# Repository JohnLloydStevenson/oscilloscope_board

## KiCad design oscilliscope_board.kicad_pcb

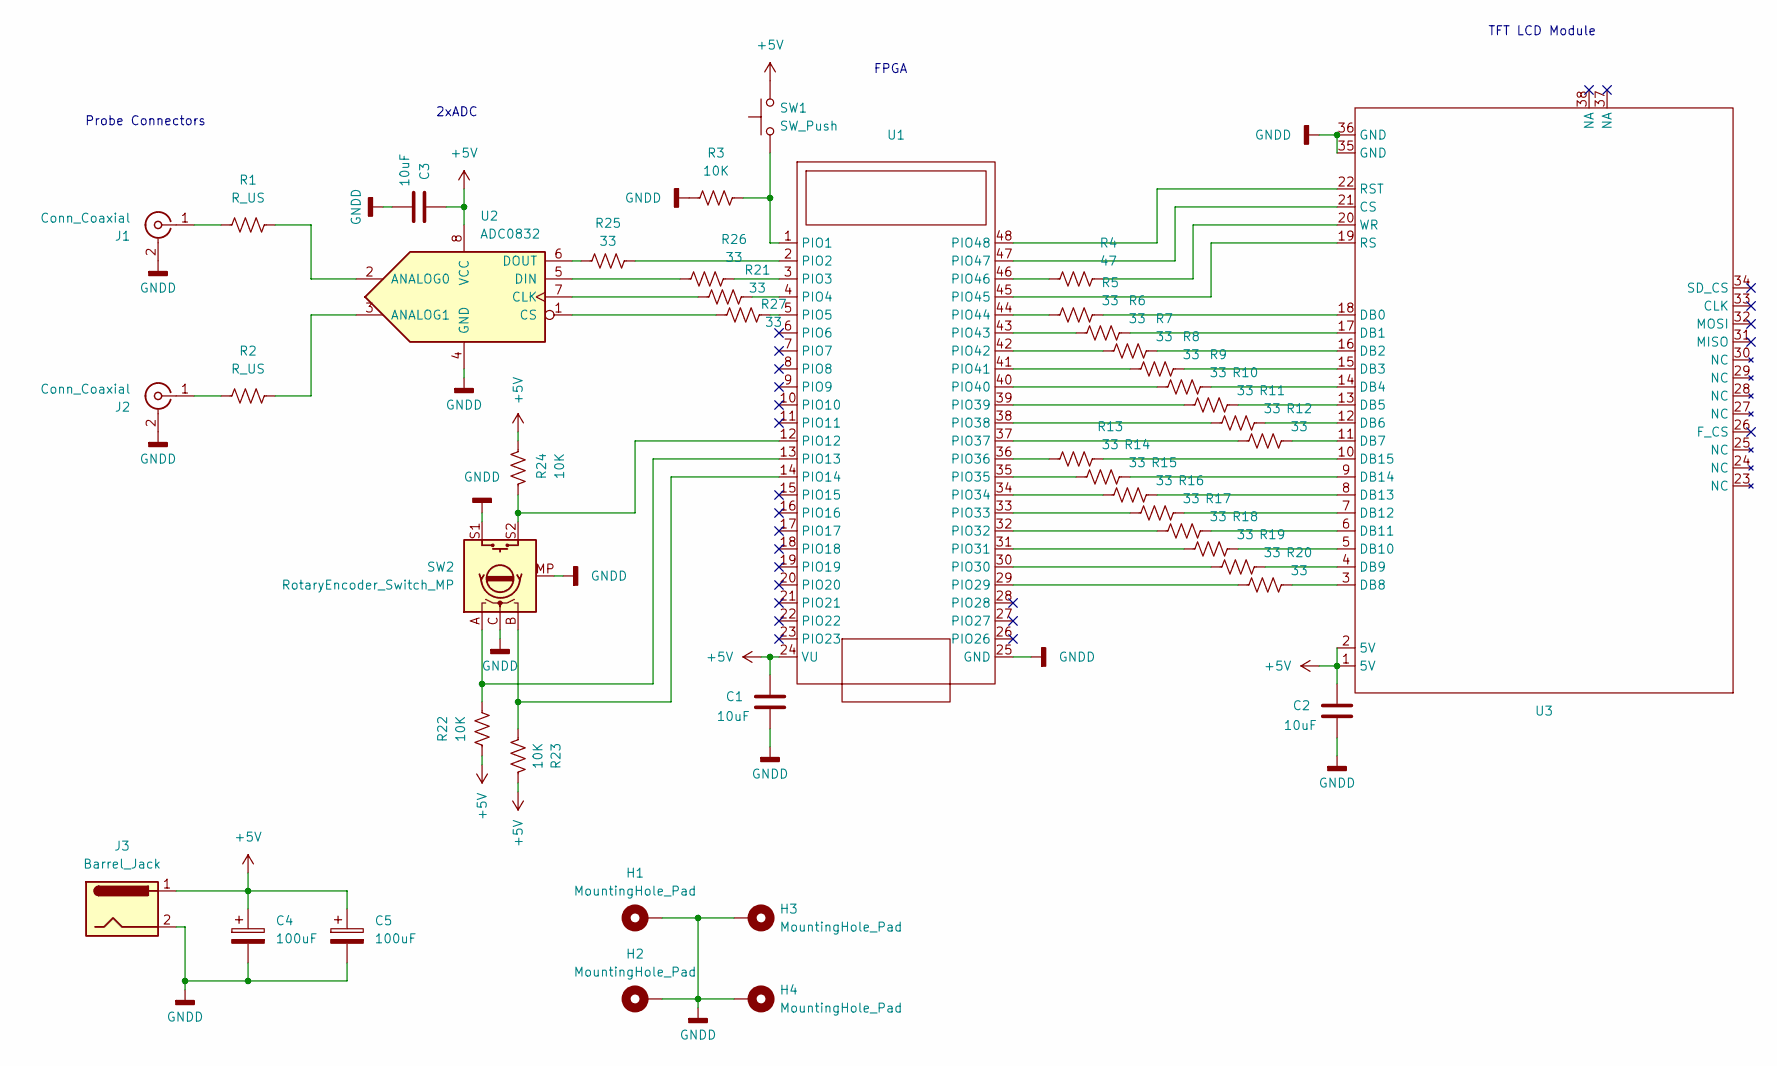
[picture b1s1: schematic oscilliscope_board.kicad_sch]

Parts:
C1, C2, C3: 10uF; C_Disc_D4.7mm_W2.5mm_P5.00mm
C4, C5: 100uF; CP_Radial_D8.0mm_P2.50mm
H1, H2, H3, H4: MountingHole_Pad; MountingHole_3.2mm_M3_DIN965_Pad
J1, J2: Conn_Coaxial; LINX_CONBNC001
J3: Barrel_Jack; BarrelJack_GCT_DCJ200-10-A_Horizontal
R1, R2: R_US; R_0805_2012Metric_Pad1.20x1.40mm_HandSolder
R3: 10K; R_1206_3216Metric_Pad1.30x1.75mm_HandSolder
R4: 47; R_0805_2012Metric_Pad1.20x1.40mm_HandSolder
R5, R6, R7, R8, R9, R10, R11, R12, R13, R14, R15, R16, R17, R18, R19, R20, R21, R25, R26, R27: 33; R_0805_2012Metric_Pad1.20x1.40mm_HandSolder
R22, R23, R24: 10K; R_0805_2012Metric_Pad1.20x1.40mm_HandSolder
SW1: SW_Push; SW_Cherry_MX_1.00u_Plate
SW2: RotaryEncoder_Switch_MP; RotaryEncoder_Bourns_Vertical_PEC12R-3x17F-Sxxxx
U1: Cmod A7 35T CPG236
U2: ADC0832; CERDIP-8_W7.62mm_SideBrazed
U3: TFT LCD 3.5 ArduinoMega Shield

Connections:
+5V: C1.1, C2.1, C3.1, C4.1, C5.1, J3.1, R22.1, R23.1, R24.1, SW1.2, U1.24 (VU), U2.8 (VCC), U3.1 (5V), U3.2 (5V)
GNDD: C1.2, C2.2, C3.2, C4.2, C5.2, H1.1, H2.1, H3.1, H4.1, J1.2 (Ext), J2.2 (Ext), J3.2, R3.1, SW2.C, SW2.MP, SW2.S1, U1.25 (GND), U2.4 (GND), U3.35 (GND), U3.36 (GND)
unnamed: J1.1 (In), R1.1
unnamed: J2.1 (In), R2.1
unnamed: R3.2, SW1.1, U1.1 (PIO1)
unnamed: R25.2, U1.2 (PIO2)
unnamed: R26.2, U1.3 (PIO3)
unnamed: R21.2, U1.4 (PIO4)
unnamed: R27.2, U1.5 (PIO5)
unnamed: R24.2, SW2.S2, U1.12 (PIO12)
unnamed: R22.2, SW2.A, U1.13 (PIO13)
unnamed: R23.2, SW2.B, U1.14 (PIO14)
unnamed: R20.1, U1.29 (PIO29)
unnamed: R19.1, U1.30 (PIO30)
unnamed: R18.1, U1.31 (PIO31)
unnamed: R17.1, U1.32 (PIO32)
unnamed: R16.1, U1.33 (PIO33)
unnamed: R15.1, U1.34 (PIO34)
unnamed: R14.1, U1.35 (PIO35)
unnamed: R13.1, U1.36 (PIO36)
unnamed: R12.1, U1.37 (PIO37)
unnamed: R11.1, U1.38 (PIO38)
unnamed: R10.1, U1.39 (PIO39)
unnamed: R9.1, U1.40 (PIO40)
unnamed: R8.1, U1.41 (PIO41)
unnamed: R7.1, U1.42 (PIO42)
unnamed: R6.1, U1.43 (PIO43)
unnamed: R5.1, U1.44 (PIO44)
unnamed: U1.45 (PIO45), U3.19 (RS)
unnamed: R4.1, U1.46 (PIO46)
unnamed: U1.47 (PIO47), U3.21 (CS)
unnamed: U1.48 (PIO48), U3.22 (RST)
unnamed: R1.2, U2.2 (ANALOG0)
unnamed: R2.2, U2.3 (ANALOG1)
unnamed: R21.1, U2.7 (CLK)
unnamed: R27.1, U2.1 (CS)
unnamed: R26.1, U2.5 (DIN)
unnamed: R25.1, U2.6 (DOUT)
unnamed: R5.2, U3.18 (DB0)
unnamed: R6.2, U3.17 (DB1)
unnamed: R7.2, U3.16 (DB2)
unnamed: R8.2, U3.15 (DB3)
unnamed: R9.2, U3.14 (DB4)
unnamed: R10.2, U3.13 (DB5)
unnamed: R11.2, U3.12 (DB6)
unnamed: R12.2, U3.11 (DB7)
unnamed: R20.2, U3.3 (DB8)
unnamed: R19.2, U3.4 (DB9)
unnamed: R18.2, U3.5 (DB10)
unnamed: R17.2, U3.6 (DB11)
unnamed: R16.2, U3.7 (DB12)
unnamed: R15.2, U3.8 (DB13)
unnamed: R14.2, U3.9 (DB14)
unnamed: R13.2, U3.10 (DB15)
unnamed: R4.2, U3.20 (WR)

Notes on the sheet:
TFT LCD Module
Probe Connectors
FPGA
2xADC

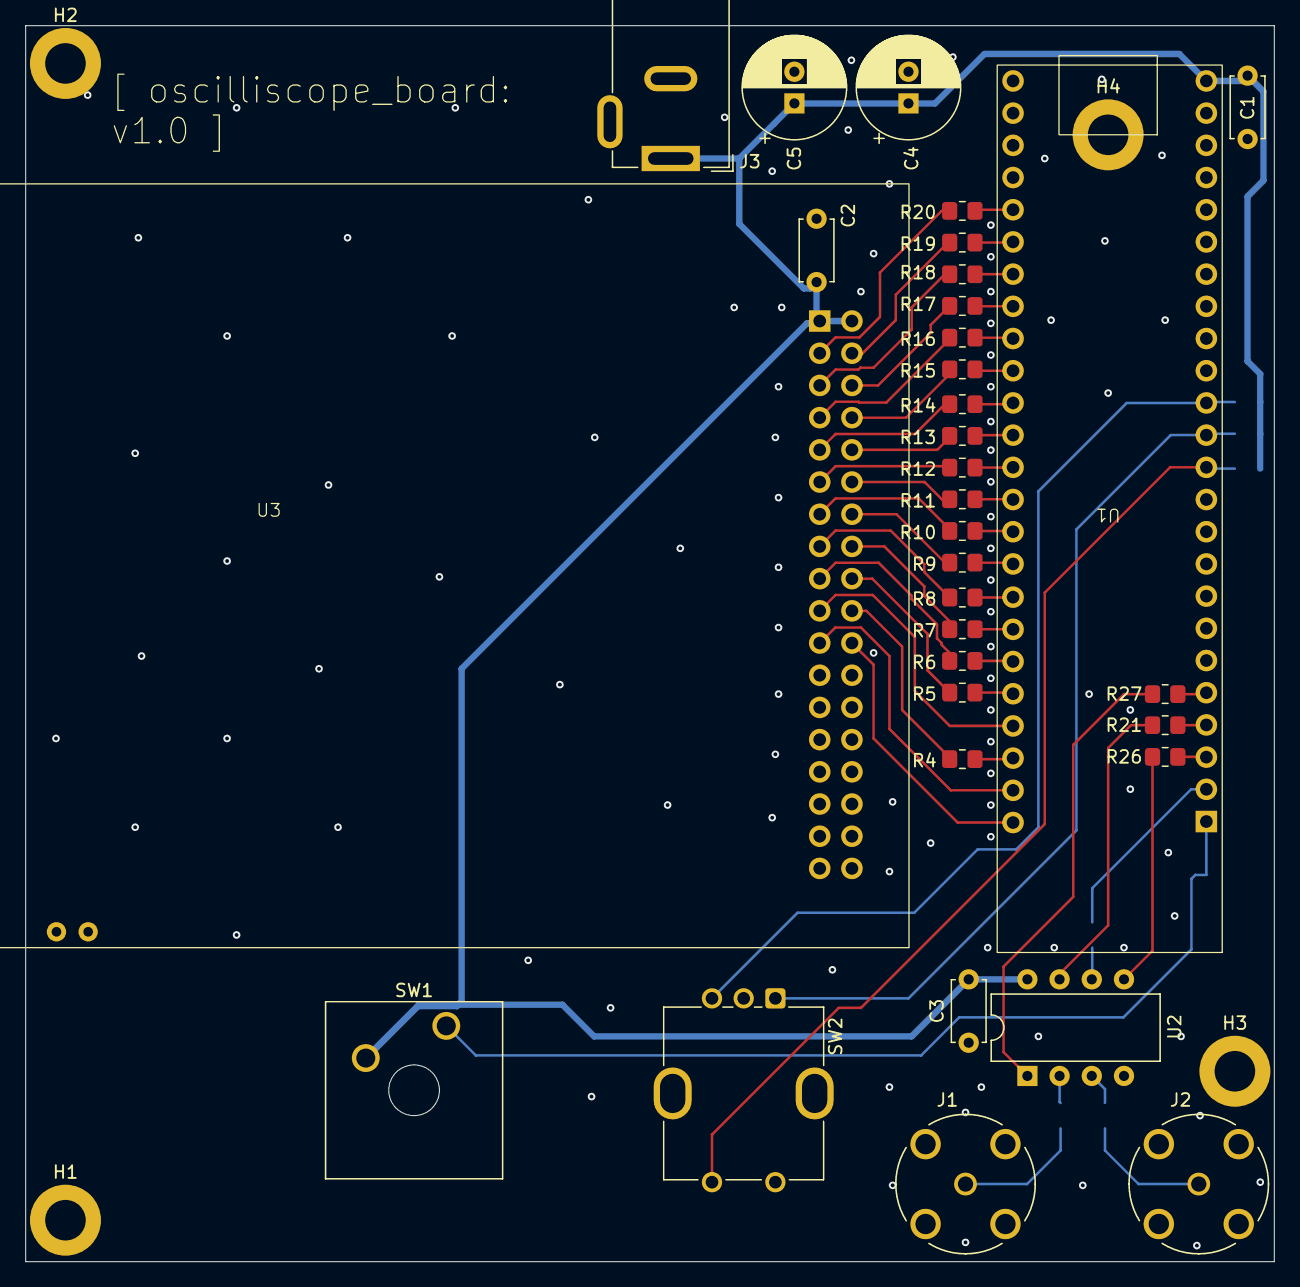
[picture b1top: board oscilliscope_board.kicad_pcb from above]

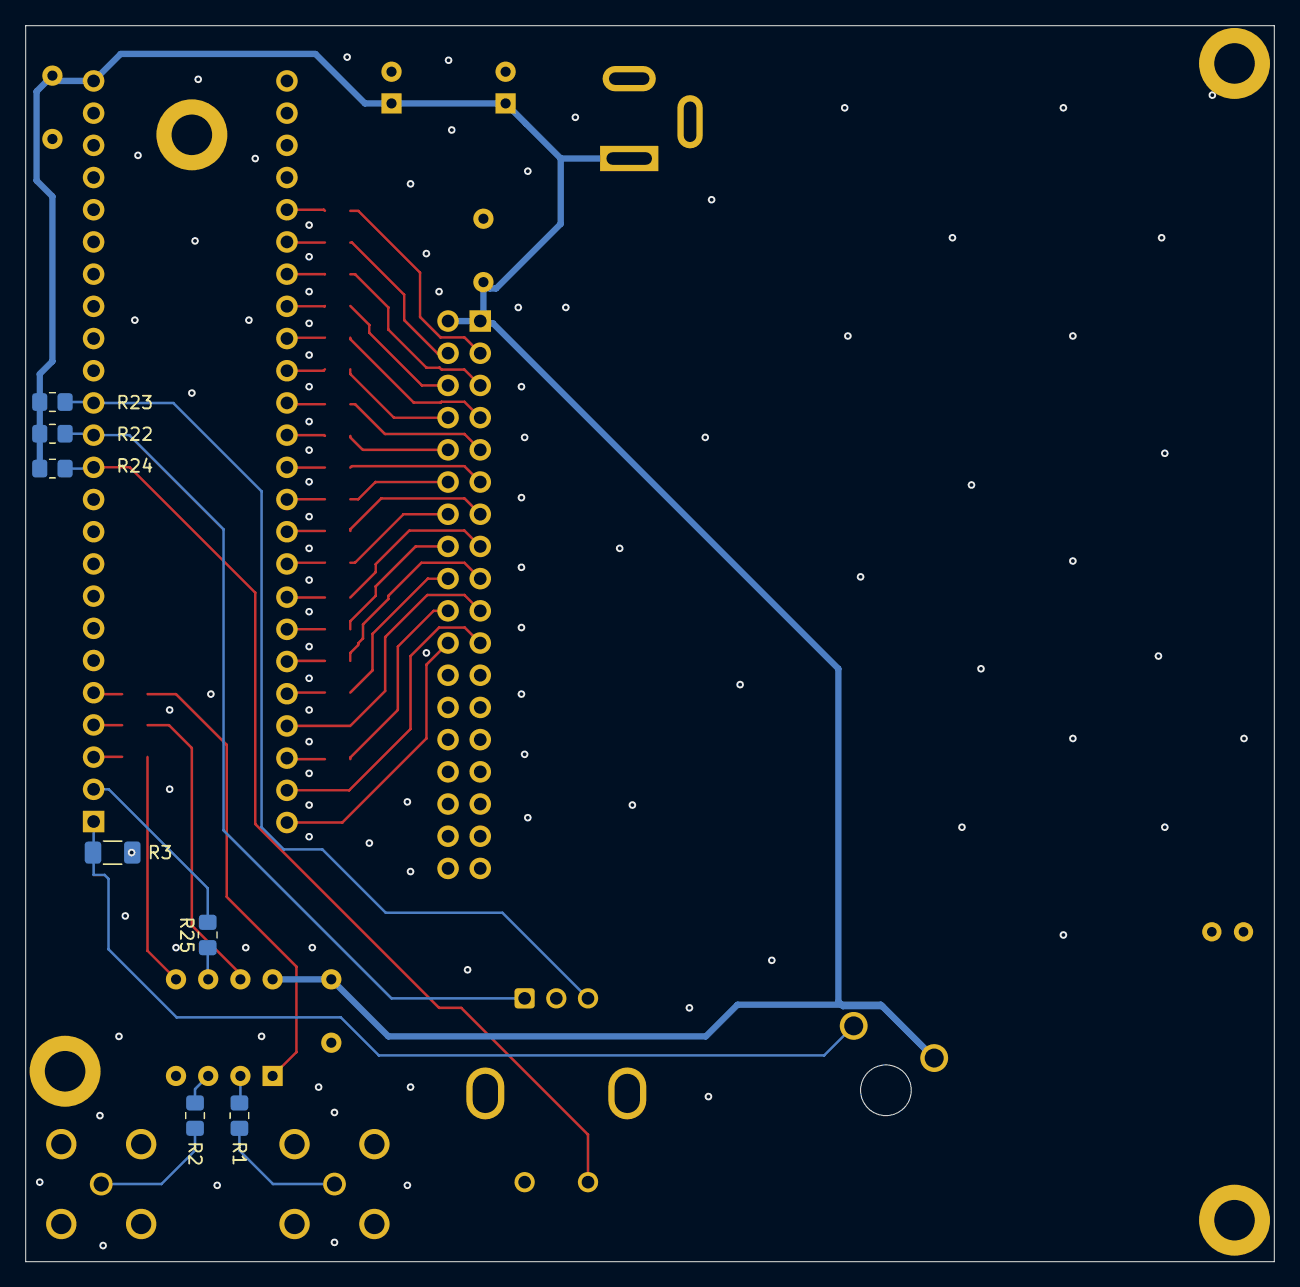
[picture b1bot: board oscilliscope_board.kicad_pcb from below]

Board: 4 copper layers, 98.5 x 97.5 mm, 44 parts (7 on the bottom side), 55 nets.

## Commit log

2025-11-21 stubbed out kicad files and added gitignore
2025-11-21 started schematic capture, created custom symbol for Digilent Cmod A7 35T
2025-11-21 new TFDT LCD Module symbol
2025-11-21 schematic capture complete
2025-11-21 new footprints for lcd shield and Xilinx fpga, assigned foorprints
2025-11-22 new footprint from digikey
2025-11-22 added rotary encoder to schematic
2025-11-22 assigned footprint
2025-11-23 new pcb file, all footprints assigned. ready to start layout
2025-11-25 routed all board connections. needs review
2025-11-25 added version to silkscreen, minor adustments
2025-11-25 gerber output settings and 1 extra via
2025-11-25 one last via
2025-11-25 added mounting holes for stand-off legs
